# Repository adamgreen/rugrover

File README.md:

# Rug Rover

## **Project on Hold**
I am putting this project on hold for a few months while I switch back to my [Robomagellan robot project](https://github.com/adamgreen/Ferdinand20/#readme) in hopes of the SRS Robothon competition being run in 2023. I will take lessons learned this year while working on my RugRover and apply them to my Robomagellan bot, Ferdinand20.

## Project Overview

When I first started pursuing robotics as a hobby back in the late 1990s, one of the first books I read was ["Mobile Robots: Inspiration to Implementation" by Joseph L. Jones and Anita M. Flynn](https://www.amazon.com/Mobile-Robots-Inspiration-Implementation-Second/dp/B0087P7X2S). I just read it again recently and the core lessons covered by the book are just as useful today as they were back at that time even though some of the technology discussed is now a bit out of date. The mechanical, electrical, motor physics, and behavior based programming topics covered are all still relevant. The Motorola 68HC11 microcontroller and Interactive C programming language are examples of some of the more dated topics.

After reading the book for the first time, I ordered one of the [Rug Warrior Pro kits](http://www.robotbooks.com/rug_warrior.htm) and assembled it. I enjoyed putting it together but never did a lot of experimentation with it as I never really got one of the wheel encoders to work properly. It seemed to pick up noise from the motor as erroneous encoder tick counts.

Having recently reread the book, I thought it would be fun to build a comparable robot using more recent technology. This Rug Rover project is my attempt to build such a robot. It features will include:
* Similar sensors/actuators:
  * Motors with encoders
  * IR proximity sensors
  * Bumper switches
  * Microphone
  * Speaker
  * Pyroelectric sensor
  * Photo Cell light level detectors
  * LCD
* Add in IR based downward facing cliff detectors so that I can run the robot in my loft and hopefully write software that stops it from trying to make a run down the stairs.
* More modern nRF52 BLE capable microcontroller:
  * Exploit the BLE capabilities of this microcontroller to enable wireless debugging and programming.
  * Program in C/C++ using GCC.
  * Debug code using GDB.
* Mechanical components will be designed in CAD and 3D printed.
* Use KiCAD to design a custom PCB for this bot. The first iteration of the PCB will be a shield for a nRF52 development kit that I already own. Later I can design a new PCB that uses a small nRF52 module, like those [offered by Adafruit](https://www.adafruit.com/product/4077).

## Reading List
In addition to reading ["Mobile Robots: Inspiration to Implementation" by Joseph L. Jones and Anita M. Flynn](https://www.amazon.com/Mobile-Robots-Inspiration-Implementation-Second/dp/B0087P7X2S) I have also read a few other books to learn more about robot design, building, and programming while working on this project:

**Note:** A free PDF version of the **Navigating Mobile Robots book by Borenstein et al** shown above is also available [here](http://www-personal.umich.edu/~johannb/Papers/pos96rep.pdf).

## Bill of Materials
| Quantity | Part Name / Link |
|---|-|
| 2 | [63:1 Metal Gearmotor 20Dx43L mm 6V CB with Extended Motor Shaft](https://www.pololu.com/product/3714) |
| 1 | [Magnetic Encoder Pair Kit for 20D mm Metal Gearmotors, 20 CPR, 2.7-18V](https://www.pololu.com/product/3499) |
| 2 | [TB9051FTG Single Brushed DC Motor Driver Carrier](https://www.pololu.com/product/2997) |
| 1 | [Pololu Multi-Hub Wheel w/Inserts for 3mm and 4mm Shafts - 80×10mm, Black, 2-Pack](https://www.pololu.com/product/3690) |
| 1 | [Supporting Swivel Caster Wheel - 1.3" Diameter](https://www.adafruit.com/product/2942) |
| 1 | [Pololu 3.3V, 500mA Step-Down Voltage Regulator D24V5F3](https://www.pololu.com/product/2842) |
| 1 | [Pololu 5V, 500mA Step-Down Voltage Regulator D24V5F5](https://www.pololu.com/product/2843) |
| 1 | [Pololu 12V Step-Up Voltage Regulator U3V40F12](https://www.pololu.com/product/4016) |
| 1 | [Adafruit I2S 3W Class D Amplifier Breakout - MAX98357A](https://www.adafruit.com/product/3006) |
| 1 | [Mini Oval Speaker - 8 Ohm 1 Watt](https://www.adafruit.com/product/3923) |
| 1 | [Adafruit PDM MEMS Microphone Breakout](https://www.adafruit.com/product/3492) |
| 1 | [Graphical OLED Display: 128x64, 1.3", White, SPI](https://www.pololu.com/product/3760) |
| 1 | [MCP23018T-E/SO - I/O Expander 16 I²C 3.4 MHz 28-SOIC](https://www.digikey.com/en/products/detail/microchip-technology/MCP23018T-E-SO/2002549) |
| 2 | [VL6180X Time-of-Flight Distance Sensor Carrier with Voltage Regulator, 60cm max](https://www.pololu.com/product/2489) |
| 5 | [VL53L1X Time-of-Flight Distance Sensor Carrier with Voltage Regulator, 400cm Max](https://www.pololu.com/product/3415) |
| 2 | [Photo cell (CdS photoresistor)](https://www.adafruit.com/product/161) |
| 3 | [Snap-Action Switch with 15.6mm Bump Lever: 3-Pin, SPDT, 5A](https://www.pololu.com/product/1405) |
| 1 | [PIR Motion Sensor](https://www.pololu.com/product/2731) |
| 1 | [Adafruit Precision NXP 9-DOF Breakout Board - FXOS8700 + FXAS21002](https://www.adafruit.com/product/3463) |
| 1 | [Diode Schottky 60 V 7A Surface Mount TO-277A ](https://www.digikey.com/en/products/detail/vishay-general-semiconductor-diodes-division/SS10P6-M3-86A/2152231) |
| 1 | [Toggle Switch SPDT Through Hole](https://www.digikey.com/en/products/detail/e-switch/100SP1T1B4M2QE/378824?s=N4IgTCBcDaIKIHEwGYCsqC0A5AIiAugL5A) |
| 1 | [Rechargeable NiMH Battery Pack: 6.0 V, 2200 mAh, 3+2 AA Cells, JR Connector](https://www.pololu.com/product/2224) |
| 2 | [Red Dirt Derby 2 oz Tungsten Putty Weights](https://www.amazon.com/Red-Dirt-Derby-Tungsten-Pinewood/dp/B06Y5FDLL6) |
| 1 | [1/4" OD Black Latex Tubing for Bumper Skirt Standoffs](https://www.amazon.com/LATEX-TUBING-602-BLACK-10FT/dp/B074NCLZSW) |
| 1 | [Nordic Semiconductor nRF52 Development Kit](https://www.digikey.com/en/products/detail/nordic-semiconductor-asa/NRF52-DK/5773879) |
| X | Already owned 0805 passives, 0.1" headers, etc. |
| X | Already owned M2, M2.5, and M3 hardware |

**Notes:** I didn't end up with enough spare pins on version 1 of the PCB to connect the microphone and I2S audio components. I will experiment with these devices off of the robot for now and then add them on the next revision of the board.

## Mechanical Design
When it comes to robot building, the mechanical portions are my weakest area. On some other robot projects I have started with software drivers and then never got around to even starting on the mechanical portions since I wasn't really looking forward to it. Best to get it out of the way first on this project. Doing it first also means that I have something physical to look at and hold earlier in the project to help keep me motivated.

**Mechanical Highlights:**
* 3D print the mechanical parts for this robot in PETG.
* Use OpenSCAD for the 3D design.
* The following parts will be mounted to the underside of the robot chassis:
  * 2 x Motors
  * 1 x Caster
  * 2 x Cliff Detection Sensors (VL6180X) mounted in front of the wheels.
  * 3 x Micro Switches to detect bumper collisions.
  * 1 x 5 cell (6V) NiMH rechargeable battery.
* Chassis has holes for attachment of following parts to the topside of the chassis:
  * 5 x Standoffs for Nordic nRF52-DK Development Kit PCB to which shield with remaining sensors/actuators will be mounted.
  * 3 x Flexible Rubber Tube Standoffs to which the bumper skirt is attached, allowing bumper to move and press against micro switches when an obstacle is encountered.
  * A separate curved cylindrical 3D printed holder that goes on the back of the robot to hold ~100g of tungsten counter weight. This moves the center of mass closer to the caster so that the robot doesn't nose dive during quick decelerations. Only having room for the batteries at the front of the bot increased the need for this counterweight.
* A separate bumper skirt is printed to enclose the robot.
  * It is mounted to the chassis on flexible rubber tube standoffs like the Rug Warrior Pro.

**Lessons Learned:**
* The [caster](https://www.adafruit.com/product/2942) I used on this robot is probably too large for the size of the robot. Its size makes it difficult to concentrate the mass over the caster by placing heavy things like the batteries near it on the bottom. I now see why the original RugWarrior Pro used the smaller non-swiveling ball caster. It took up less space and allowed the battery pack to be placed between the axle and the caster.
* [Tungsten putty](https://www.amazon.com/Red-Dirt-Derby-Tungsten-Pinewood/dp/B06Y5FDLL6) is actually a soft moving liquid. The putty I placed in the cylindrical 3D printed holder at the back of the robot leaked out over time and some of it flowed out into the rear micro switch. I was able to take the robot apart and clean up the leaked putty. I designed and printed a bottom for the holder that I welded in place with a soldering iron to contain the tungsten putty inside.

## Electronics Design
Once I had the mechanical design mostly figured out, I moved onto the design of the electronics in [KiCad](https://www.kicad.org).

**Electronic Highlights:**
* The initial version of the electronics will use the [Nordic nRF52 DK](https://www.nordicsemi.com/Products/Development-hardware/nrf52-dk) as its base and the custom robot electronics will be added as a custom shield.
* The shield design is 4-layer to make it easier to route the signals all around the board without worrying about ground and power. The layout is a bit complicated as the Arduino header format used by the nRF52 DK has most of the signals on one side of the board but I want to place input/output connectors on both sides of the board.
* Most of the sensors and actuators are connected to the PCB via 0.1" headers.
* Version 1 of the shield includes:
  * Dual TB9051FTG motor controllers
  * Quadrature motor encoders
  * Dual photo cells
  * PIR motion sensor
  * Three switches for bumper skirt obstacle detection
  * SPI based OLED screen
  * One I2C bus for connection to:
    * 5 x VL53L1X ToF Obstacle Detection Sensors (3 front facing & 2 back facing).
    * 2 x VL6180X ToF Cliff Detection Sensors mounted in front of the wheels.
    * 1 x Adafruit Precision NXP 9-DOF IMU
    * 1 x 16 channel MCP23018 I/O port expander used for:
      * Asserting VL53L1X and VL6180X XSHUT pins to init each one separately and give them unique I2C addresses.
      * Reading of the multiple VL53L1X and VL6180X GPIO pins.
 * Multiple voltage supplies:
   * 6V Directly from Batteries for Motors
   * 5V from Buck Regulator for TB9051FTG Motor Controllers
   * 12V from Boost Regulator for PIR Sensor
   * 3.3V from Buck Regulator for rest of Electronics

</br>

[Schematic PDF](hardware/shield.pdf)</br>

## Software
Once the mechanical and electronics were far enough along I could start writing the software. This should be where I spend the most amount of time. I will provide links to notes about each software component as I write its code.

**Software Components:**
* [mriblue Debug Monitor](mriblue/README.md#mriblue): A FLASH resident bootloader and debug monitor that runs on the nRF52832 to enable wireless debugging and programming over Bluetooth Low Energy (BLE) from GDB.
* [SH1106 SPI based OLED Driver](software/OLED_SH1106/):
  * An [Adafruit GFX](https://github.com/adafruit/Adafruit-GFX-Library) based display driver.
  * The drawing primitives just modify an in-memory version of the display's frame buffer.
  * A separate refresh() method is used to copy that frame buffer to the SH1106 OLED driver.
  * The refresh() copy makes use of the nRF52's SPI Master peripheral's EasyDMA functionality to perform most of this SPI transfer in the background with little CPU intervention. The CPU is just used to setup the transfer for each of the 8 frame buffer pages.
* [QuadratureDecoderHardware](software/QuadratureDecoder/QuadratureDecoderHardware.h): This driver uses the QDEC peripheral on the nRF52832 to count quadrature encoder ticks. It requires almost no CPU cycles but there is only 1 instance on the microcontroller so I use it for the left encoder only.
* [QuadratureDecoderSoftware](software/QuadratureDecoder/QuadratureDecoderSoftware.h): This driver uses the GPIOTE to fire an ISR on each edge of both the A and B signals from a quadrature encoder. The ISR uses the previous and current encoder signal states to determine if the count should be incremented or decremented. A maximum of 4 encoders can make use of this library if nothing else is making use of the nRF52's 8 GPIOTE channels. The driver needs 2 GPIOTE channels for each encoder, 1 per encoder signal.
* [SAADCScanner](software/SAADCScanner/SAADCScanner.h): This driver runs in the background, reading the specified analog channels (up to 8 on the nRF52832) in a loop using the nRF52's SAADC peripheral:
  * At the end of each loop, an ISR is triggered to process the most current readings. This allows for minimal CPU overhead.
  * It can be configured for manual scanning rather than continuously scanning in the background. I am currently using it this way since it would run at 50kHz in auto mode and the ISR kept showing up in call stacks when I profiled the code.
  * The application can read out a channel's value at a rate slower than the ISR firing rate. The returned structure contains the minimum, maximum, and mean values seen since the last read.
  * The application can also specify trigger limits for the minimum and/or maximum analog values to be expected. Readings outside of these limits will be tracked in the returned structure and can also trigger a callback to a caller provided ISAADCScannerNotification interface.
  * This driver is currently only used to monitor the motor currents for each wheel. In the future it can be used to monitor the light levels detected by the 2 photocells.
* [DualTB9051FTGDrivers](software/DualTB9051FTGDrivers/DualTB9051FTGDrivers.h): This driver allows for the control of 2 Toshiba TB9051FTG H-bridge chips, one for each motor on the robot. It uses 4 channels of the nRF52's PWM peripheral to control the torque and speed of the motors with minimal CPU intervention.
* [GlobalTimer](software/GlobalTimer/GlobalTimer.h): Uses TIMER2 to implement an Arduino like ```micros()``` API to return a 32-bit value indicating the number of microseconds since reset.
* [PID](software/PID/PID.h): Header only class that implements a PID (proportional, integral, derivative) algorithm. It is inspired by [Brett Beauregard's Arduino PID Library](https://github.com/br3ttb/Arduino-PID-Library/) and the [PID e-book available on controlguru](http://www.controlguru.com).
* [DifferentialDrive](software/DifferentialDrive/DifferentialDrive.h): This driver implements closed loop control of RugRover's differential drive. It is built on top of the **DualTB9051FTGDrivers** and Quadrature Decoder libraries. It also has a getStats() method which exposes internal state of the motors, encoders, and PID algorithm to the user:
  * The requested velocity and the actual measured velocity of each wheel.
  * The running total of encoder ticks for each wheel.
  * The motor power (-100% to 100%) being used for each wheel.
  * The most recent motor current measurement (mA) taken for each wheel.
  * The maximum motor current measurement (mA) taken for each wheel so far.
  * Whether any motor faults or over-current events have been detected by the motor drivers.
  * The mAh consumed by the motors since reset.
  * A flag to indicate whether the PID is running in manual or auto mode.
* [Navigate](software/Navigate/README.md#navigate-class): Class used to navigate between a list of user specified waypoints and track the real world location of the robot based on wheel odometry.
* [CircularBuffer](software/CircularBuffer/CircularBuffer.h): Generic lock-free circular buffer that supports multiple producers and consumers.
* [I2CAsync](software/I2CAsync/I2CAsync.h): This driver makes it easier to use the nRF52's TWIM peripheral asynchronously. It makes use of the `CircularBuffer` to allow ISRs running at different interrupt priorities to communicate with several different I2C devices.
* [AdafruitPrecision9DoF](software/AdafruitPrecision9DoF/AdafruitPrecision9DoF.h): This driver uses the `I2CAsync` driver to communicate with the `FXOS8700CQ` accelerometers/magnetometers and the `FXAS21002C` gyros.
  * The desired refresh rate (100Hz, 200Hz, or 400Hz) is specified in the constructor.
  * The `FXOS8700CQ` will pull a pin low when the next sample is ready at the specified rate.
  * This falling edge generates an interrupt that causes the next I2C reads of the accelerometers, magnetometers, and gyros to be queued up in the `I2CAsync` queue.
  * The `getRawSensorValues()` method, typically called from the main thread, will block until all of the queued up reads are completed.
* [OrientationKalmanFilter](software/KalmanFilter/OrientationKalmanFilter.h): Implements a Kalman filter which takes the raw accelerometer, magnetometer, and gyro measurements from the `AdafruitPrecision9DoF` object and generates a 3D orientation quaternion.
  * It also contains a method which can extract the compass heading from this 3D orientation as well.
  * The code for this filter was based on what I learned from reading ["Kalman Filter for Beginners with MATLAB Examples" by Phil Kim](https://www.amazon.com/Kalman-Filter-Beginners-MATLAB-Examples/dp/1463648359). The system model used in this filter came from Chapter 13 of this book.
  * I documented many of the required calibration steps [earlier while working on my Ferdinand14 project](https://github.com/adamgreen/Ferdinand14#august-19-2014).
  * The [processing/calibration folder](processing/calibration/) contains a port of the calibration program which will work with this robot. The robot does need to be running the "Test IMU Raw" option from the debug menu to send the required measurements to this calibration program.
  * The [processing/orientation folder](processing/orientation/) contains a program that visualizes the 3D orientation of the robot in real time. The robot needs to be running the "Test IMU Orientation" option from the debug menu in order to send the required quaternion data over BLE to this program.
  * Both of the processing programs above use a TCP/IP socket to connect to the `mriblue` program on port 3334. This gives it access to extra data sent from the robot over BLE that isn't meant for GDB.
* [HeadingKalmanFilter](software/KalmanFilter/HeadingKalmanFilter.h): Implements a Kalman filter which fuses Z axis gyro angular rate measurements with angle heading change measurements calculated from wheel odometry.
  * The code for this filter was also based on what I learned from reading ["Kalman Filter for Beginners with MATLAB Examples" by Phil Kim](https://www.amazon.com/Kalman-Filter-Beginners-MATLAB-Examples/dp/1463648359).
  * The system model used by this filter was one I created on my own. It tracks:
    * The current heading angle in radians.
    * The current gyro angular turn rate in radians/sec.
    * The estimate of the gyro drift in radians/sec. Having an estimate of this value allows for the filter to obtain a more accurate turn rate from the gyro than possible otherwise.
  * I determined the first two variance values to place in the Q matrix by setting the `DEBUG_CALCULATE_STATS_FOR_SYSTEM_MODEL` macro to true in [main.cpp](software/main.cpp) so that it would dump stats about how much this model tended to deviate from the real world while just using wheel odometry. I then set the variance for the drift parameter to 0.0 since the model maintains it as a constant and in the real world it should vary slowly over time.
  * The `GYRO_ERROR` was calculated and dumped by the orientation.pde utility while I was calibrating the IMU for the OrientationKalmanFilter.
  * I estimate that the `ODOMETRY_ERROR` error is typically the result of a +/- 1 encoder tick's influence on the wheel odometry calculation of the heading angle delta.

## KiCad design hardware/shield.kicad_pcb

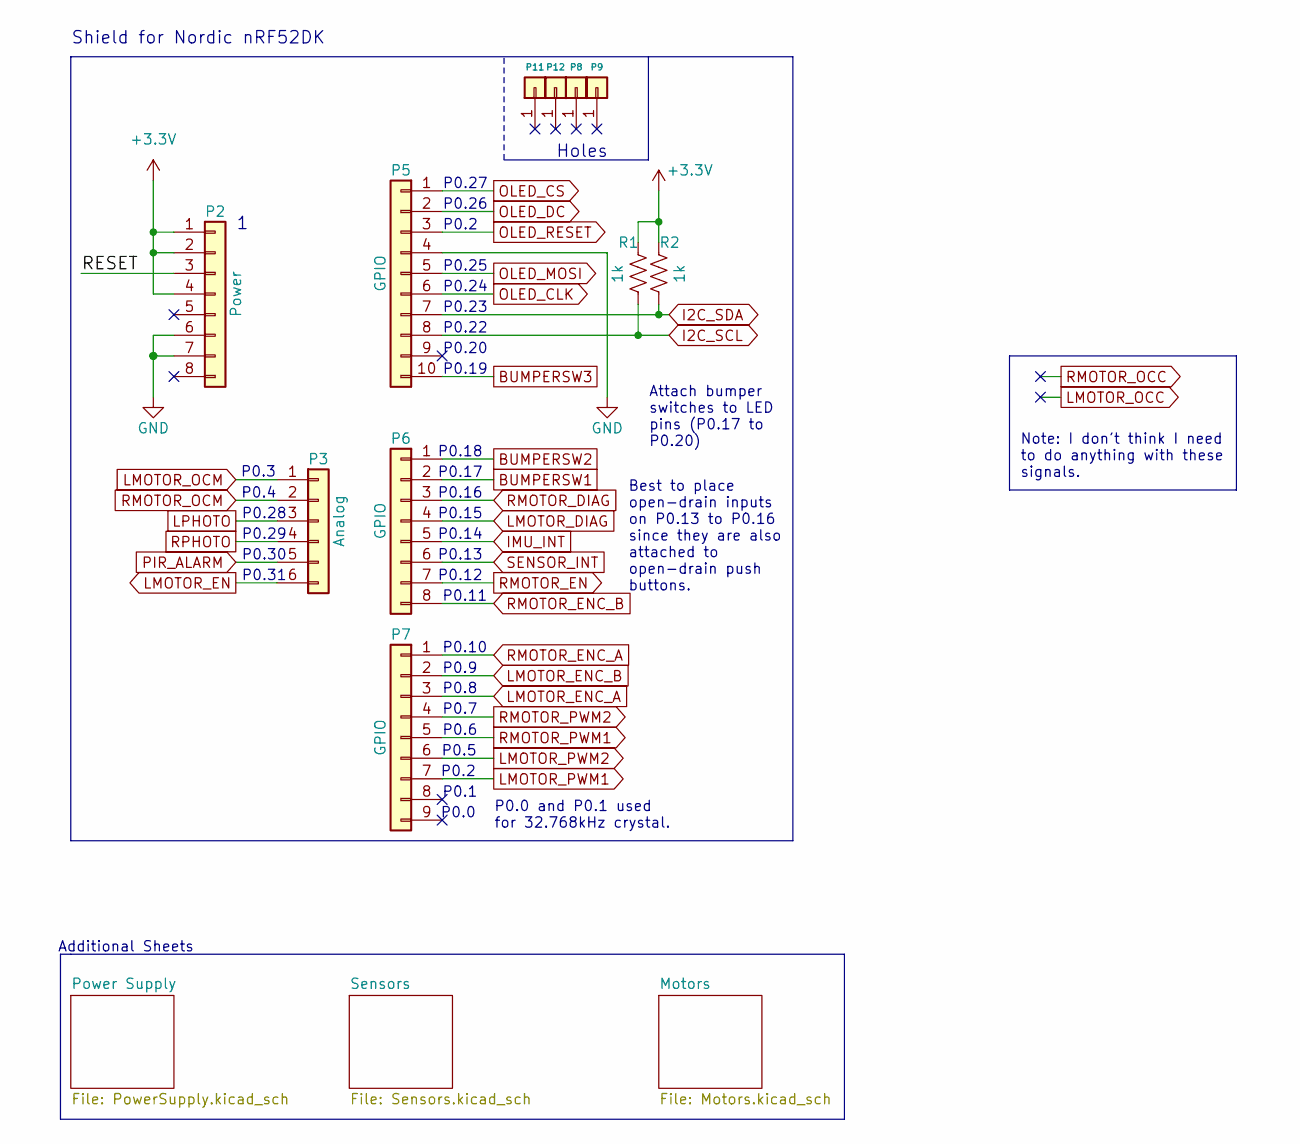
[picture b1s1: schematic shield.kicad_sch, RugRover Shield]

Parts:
P2: Power; PinHeader_1x08_P2.54mm_Vertical
P3: Analog; PinHeader_1x06_P2.54mm_Vertical
P5: GPIO; PinHeader_1x10_P2.54mm_Vertical
P6: GPIO; PinHeader_1x08_P2.54mm_Vertical
P7: GPIO; PinHeader_1x09_P2.54mm_Vertical
P8, P9, P11, P12: CONN_01X01; Arduino_1pin
R1, R2: 1k; R_0805_2012Metric_Pad1.20x1.40mm_HandSolder

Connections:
+3V3: P2.1, P2.2, P2.4, R1.1, R2.1; also elsewhere on the board
/RESET: P2.3
BUMPERSW1: P6.2; also elsewhere on the board
BUMPERSW2: P6.1; also elsewhere on the board
BUMPERSW3: P5.10; also elsewhere on the board
GND: P2.6, P2.7, P5.4; also elsewhere on the board
I2C_SCL: P5.8, R1.2; also elsewhere on the board
I2C_SDA: P5.7, R2.2; also elsewhere on the board
IMU_INT: P6.5; also elsewhere on the board
LMOTOR_DIAG: P6.4; also elsewhere on the board
LMOTOR_EN: P3.6; also elsewhere on the board
LMOTOR_ENC_A: P7.3; also elsewhere on the board
LMOTOR_ENC_B: P7.2; also elsewhere on the board
LMOTOR_OCM: P3.1; also elsewhere on the board
LMOTOR_PWM1: P7.7; also elsewhere on the board
LMOTOR_PWM2: P7.6; also elsewhere on the board
LPHOTO: P3.3; also elsewhere on the board
OLED_CLK: P5.6; also elsewhere on the board
OLED_CS: P5.1; also elsewhere on the board
OLED_DC: P5.2; also elsewhere on the board
OLED_MOSI: P5.5; also elsewhere on the board
OLED_RESET: P5.3; also elsewhere on the board
PIR_ALARM: P3.5; also elsewhere on the board
RMOTOR_DIAG: P6.3; also elsewhere on the board
RMOTOR_EN: P6.7; also elsewhere on the board
RMOTOR_ENC_A: P7.1; also elsewhere on the board
RMOTOR_ENC_B: P6.8; also elsewhere on the board
RMOTOR_OCM: P3.2; also elsewhere on the board
RMOTOR_PWM1: P7.5; also elsewhere on the board
RMOTOR_PWM2: P7.4; also elsewhere on the board
RPHOTO: P3.4; also elsewhere on the board
SENSOR_INT: P6.6; also elsewhere on the board

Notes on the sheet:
P0.24
P0.11
Attach bumper switches to LED pins (P0.17 to P0.20)
P0.14
P0.9
Note: I don't think I need to do anything with these signals.
P0.19
P0.12
P0.22
P0.30
P0.18
P0.5
P0.2
P0.20
Best to place open-drain inputs on P0.13 to P0.16 since they are also attached to open-drain push buttons.
P0.6
P0.23
P0.16
P0.17
P0.0 and P0.1 used for 32.768kHz crystal.
P0.4
P0.1
P0.31
P0.27
P0.15
P0.26
P0.3
P0.29
P0.8
P0.7
Holes
P0.13
P0.10
Additional Sheets
P0.25
P0.0
P0.28
Shield for Nordic nRF52DK

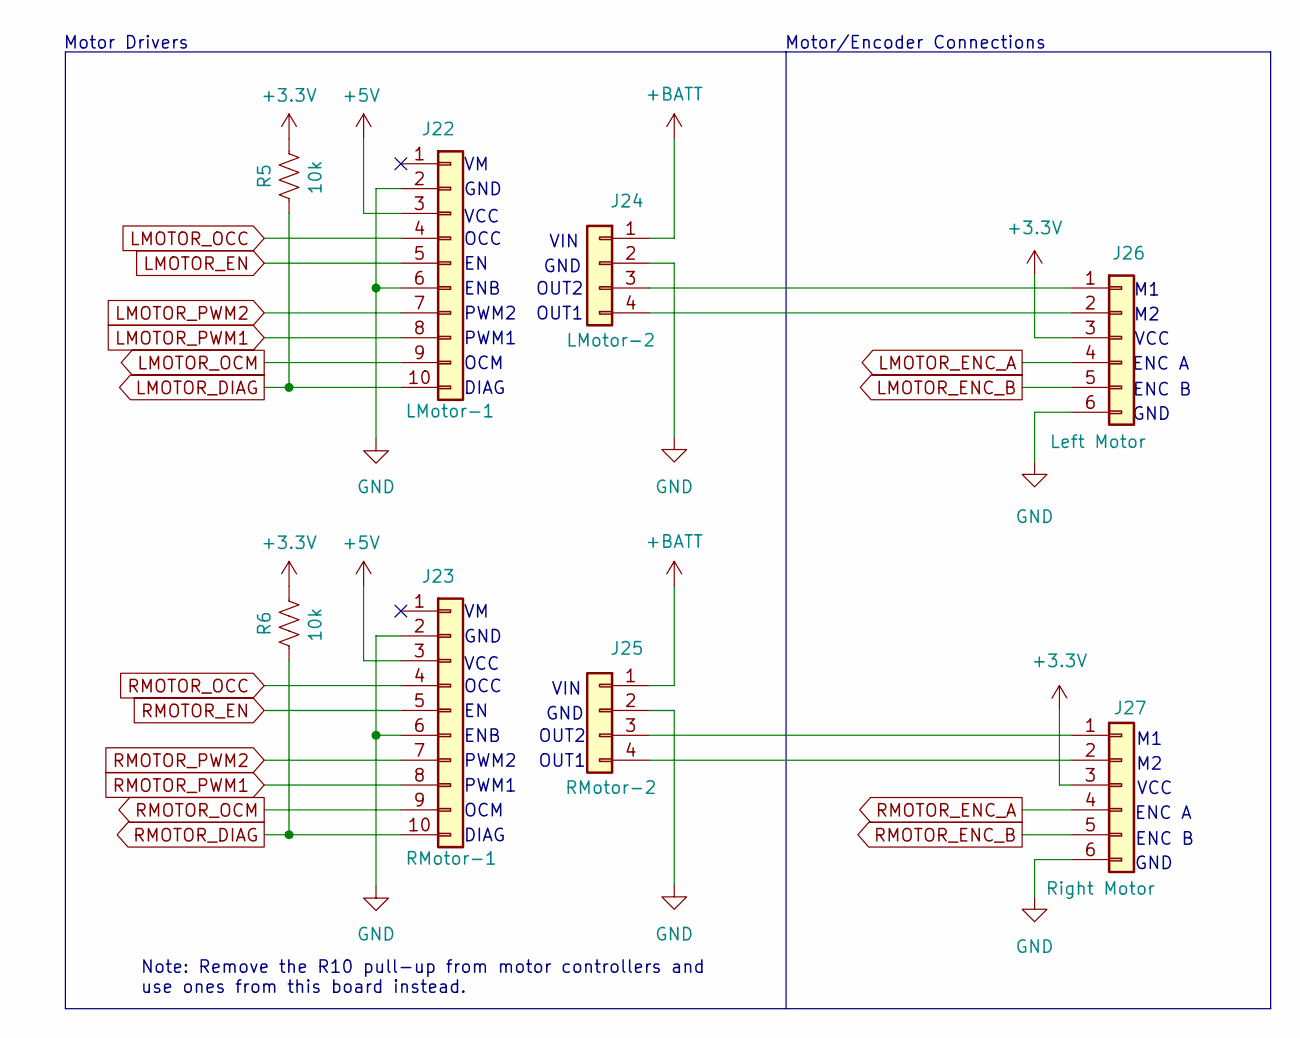
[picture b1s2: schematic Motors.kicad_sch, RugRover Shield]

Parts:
J22: LMotor-1; PinSocket_1x10_P2.54mm_Vertical
J23: RMotor-1; PinSocket_1x10_P2.54mm_Vertical
J24: LMotor-2; PinSocket_1x04_P2.54mm_Vertical
J25: RMotor-2; PinSocket_1x04_P2.54mm_Vertical
J26: Left Motor; PinSocket_1x06_P2.54mm_Horizontal
J27: Right Motor; PinSocket_1x06_P2.54mm_Horizontal
R5, R6: 10k; R_0805_2012Metric_Pad1.20x1.40mm_HandSolder

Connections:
+3V3: J26.3, J27.3, R5.2, R6.2; also elsewhere on the board
+5V: J22.3, J23.3; also elsewhere on the board
+BATT: J24.1, J25.1; also elsewhere on the board
GND: J22.2, J22.6, J23.2, J23.6, J24.2, J25.2, J26.6, J27.6; also elsewhere on the board
LMOTOR_DIAG: J22.10, R5.1; also elsewhere on the board
LMOTOR_EN: J22.5; also elsewhere on the board
LMOTOR_ENC_A: J26.4; also elsewhere on the board
LMOTOR_ENC_B: J26.5; also elsewhere on the board
LMOTOR_OCC: J22.4
LMOTOR_OCM: J22.9; also elsewhere on the board
LMOTOR_PWM1: J22.8; also elsewhere on the board
LMOTOR_PWM2: J22.7; also elsewhere on the board
unnamed: J24.3, J26.1
unnamed: J24.4, J26.2
unnamed: J25.3, J27.1
unnamed: J25.4, J27.2
RMOTOR_DIAG: J23.10, R6.1; also elsewhere on the board
RMOTOR_EN: J23.5; also elsewhere on the board
RMOTOR_ENC_A: J27.4; also elsewhere on the board
RMOTOR_ENC_B: J27.5; also elsewhere on the board
RMOTOR_OCC: J23.4
RMOTOR_OCM: J23.9; also elsewhere on the board
RMOTOR_PWM1: J23.8; also elsewhere on the board
RMOTOR_PWM2: J23.7; also elsewhere on the board

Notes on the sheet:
GND
OUT2
ENC A
PWM2
DIAG
VCC
ENB
ENC B
PWM1
Note: Remove the R10 pull-up from motor controllers and use ones from this board instead.
VIN
Motor Drivers
OUT1
OCC
Motor/Encoder Connections
OCM

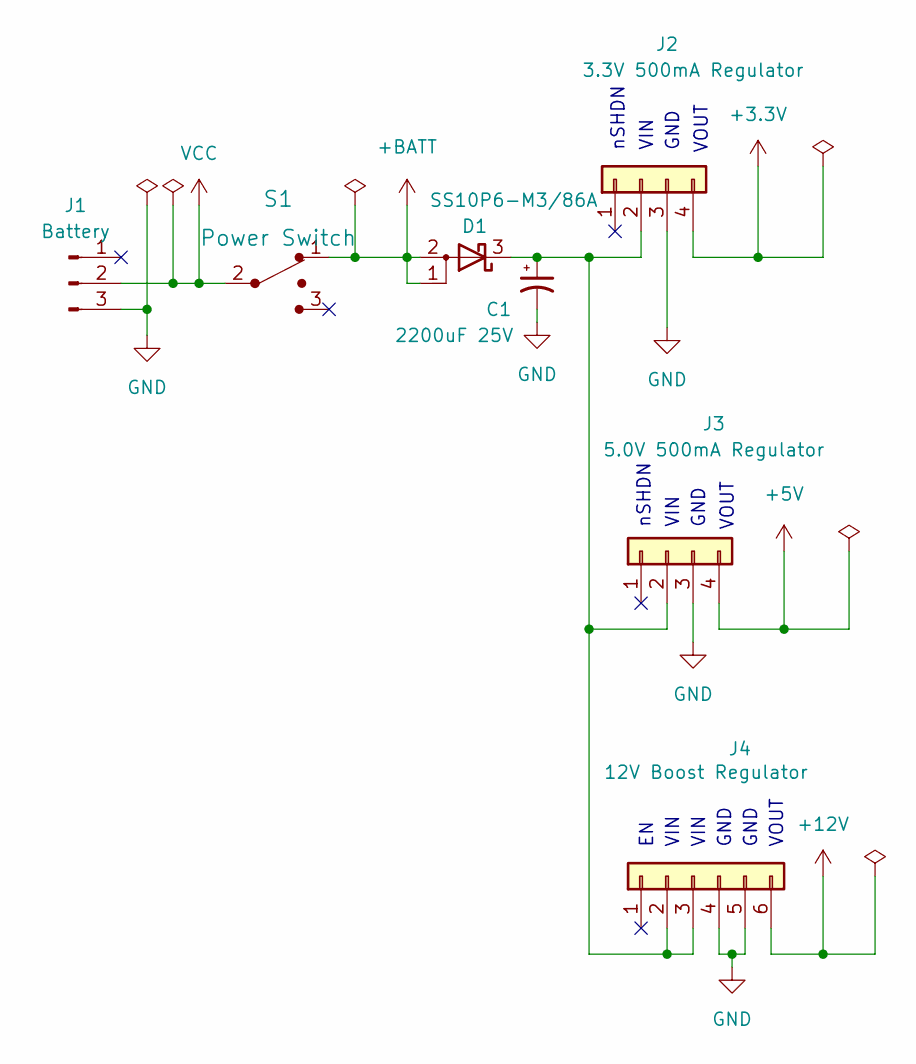
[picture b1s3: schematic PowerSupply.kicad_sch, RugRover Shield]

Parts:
C1: 2200uF 25V; CP_Radial_D13.0mm_P5.00mm
D1: SS10P6-M3/86A; TO-277A
J1: Battery; PinHeader_1x03_P2.54mm_Horizontal
J2: 3.3V 500mA Regulator; PinSocket_1x04_P2.54mm_Vertical
J3: 5.0V 500mA Regulator; PinSocket_1x04_P2.54mm_Vertical
J4: 12V Boost Regulator; PinSocket_1x06_P2.54mm_Vertical
S1: Power Switch; Toggle_Switch_100SP1T1B4M2QE; MPN 100SP1T1B4M2QE; Digi-Key_PN EG2355-ND

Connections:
+3V3: J2.4; also elsewhere on the board
+5V: J3.4; also elsewhere on the board
+12V: J4.6; also elsewhere on the board
+BATT: D1.1 (A), D1.2 (A), S1.1; also elsewhere on the board
GND: C1.2, J1.3, J2.3, J3.3, J4.4, J4.5; also elsewhere on the board
unnamed: C1.1, D1.3 (K), J2.2, J3.2, J4.2, J4.3
VCC: J1.2, S1.2 (Com)

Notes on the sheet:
VIN
GND
VOUT
nSHDN

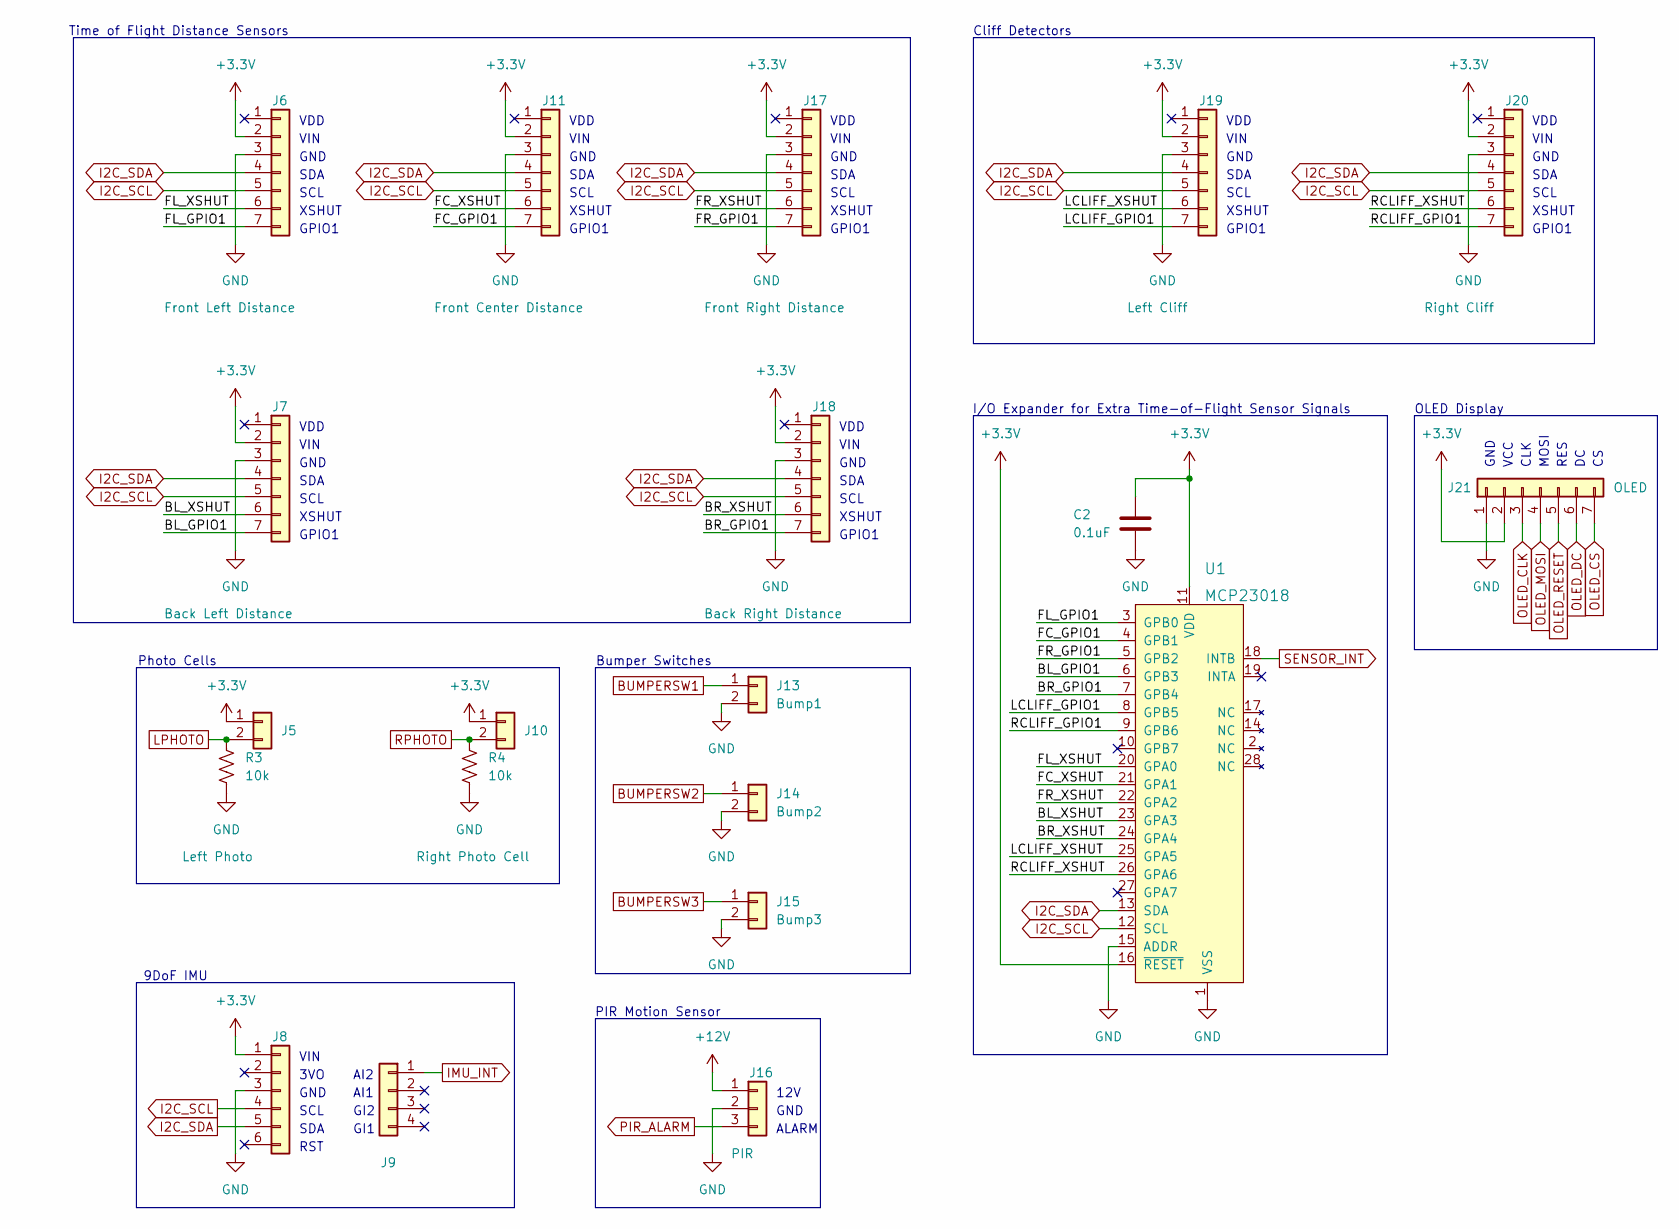
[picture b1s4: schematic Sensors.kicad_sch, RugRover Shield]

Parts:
C2: 0.1uF; C_0805_2012Metric_Pad1.18x1.45mm_HandSolder
J5: Left Photo; PinSocket_1x02_P2.54mm_Vertical
J6: Front Left Distance; PinSocket_1x07_P2.54mm_Vertical
J7: Back Left Distance; PinSocket_1x07_P2.54mm_Vertical
J8: IMU-1; PinSocket_1x06_P2.54mm_Vertical
J9: IMU-2; PinSocket_1x04_P2.54mm_Vertical
J10: Right Photo Cell; PinSocket_1x02_P2.54mm_Vertical
J11: Front Center Distance; PinSocket_1x07_P2.54mm_Vertical
J13: Bump1; PinSocket_1x02_P2.54mm_Horizontal
J14: Bump2; PinSocket_1x02_P2.54mm_Horizontal
J15: Bump3; PinSocket_1x02_P2.54mm_Horizontal
J16: PIR; PinSocket_1x03_P2.54mm_Vertical
J17: Front Right Distance; PinSocket_1x07_P2.54mm_Vertical
J18: Back Right Distance; PinSocket_1x07_P2.54mm_Vertical
J19: Left Cliff; PinSocket_1x07_P2.54mm_Horizontal
J20: Right Cliff; PinSocket_1x07_P2.54mm_Horizontal
J21: OLED; PinSocket_1x07_P2.54mm_Vertical
R3, R4: 10k; R_0805_2012Metric_Pad1.20x1.40mm_HandSolder
U1: MCP23018; SOIC-28W_7.5x17.9mm_P1.27mm; MPN MCP23018-E/SP; Digi-Key_PN MCP23018-E/SP-ND

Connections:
+3V3: C2.1, J5.1, J6.2, J7.2, J8.1, J10.1, J11.2, J17.2, J18.2, J19.2, J20.2, J21.2, U1.11 (VDD), U1.16 (~RESET); also elsewhere on the board
+12V: J16.1; also elsewhere on the board
/Sensors/BL_GPIO1: J7.7, U1.6 (GPB3)
/Sensors/BL_XSHUT: J7.6, U1.23 (GPA3)
/Sensors/BR_GPIO1: J18.7, U1.7 (GPB4)
/Sensors/BR_XSHUT: J18.6, U1.24 (GPA4)
/Sensors/FC_GPIO1: J11.7, U1.4 (GPB1)
/Sensors/FC_XSHUT: J11.6, U1.21 (GPA1)
/Sensors/FL_GPIO1: J6.7, U1.3 (GPB0)
/Sensors/FL_XSHUT: J6.6, U1.20 (GPA0)
/Sensors/FR_GPIO1: J17.7, U1.5 (GPB2)
/Sensors/FR_XSHUT: J17.6, U1.22 (GPA2)
/Sensors/LCLIFF_GPIO1: J19.7, U1.8 (GPB5)
/Sensors/LCLIFF_XSHUT: J19.6, U1.25 (GPA5)
/Sensors/RCLIFF_GPIO1: J20.7, U1.9 (GPB6)
/Sensors/RCLIFF_XSHUT: J20.6, U1.26 (GPA6)
BUMPERSW1: J13.1; also elsewhere on the board
BUMPERSW2: J14.1; also elsewhere on the board
BUMPERSW3: J15.1; also elsewhere on the board
GND: C2.2, J6.3, J7.3, J8.3, J11.3, J13.2, J14.2, J15.2, J16.2, J17.3, J18.3, J19.3, J20.3, J21.1, R3.2, R4.2, U1.1 (VSS), U1.15 (ADDR); also elsewhere on the board
I2C_SCL: J6.5, J7.5, J8.4, J11.5, J17.5, J18.5, J19.5, J20.5, U1.12 (SCL); also elsewhere on the board
I2C_SDA: J6.4, J7.4, J8.5, J11.4, J17.4, J18.4, J19.4, J20.4, U1.13 (SDA); also elsewhere on the board
IMU_INT: J9.1; also elsewhere on the board
LPHOTO: J5.2, R3.1; also elsewhere on the board
OLED_CLK: J21.3; also elsewhere on the board
OLED_CS: J21.7; also elsewhere on the board
OLED_DC: J21.6; also elsewhere on the board
OLED_MOSI: J21.4; also elsewhere on the board
OLED_RESET: J21.5; also elsewhere on the board
PIR_ALARM: J16.3; also elsewhere on the board
RPHOTO: J10.2, R4.1; also elsewhere on the board
SENSOR_INT: U1.18 (INTB); also elsewhere on the board

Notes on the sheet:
VIN
SDA
I/O Expander for Extra Time-of-Flight Sensor Signals
GND
GI1
XSHUT
GPIO1
RES
VDD
12V
CLK
SCL
Photo Cells
RST
Time of Flight Distance Sensors
AI1
OLED Display
GI2
PIR Motion Sensor
Bumper Switches
9DoF IMU
AI2
ALARM
3VO
Cliff Detectors
MOSI
VCC

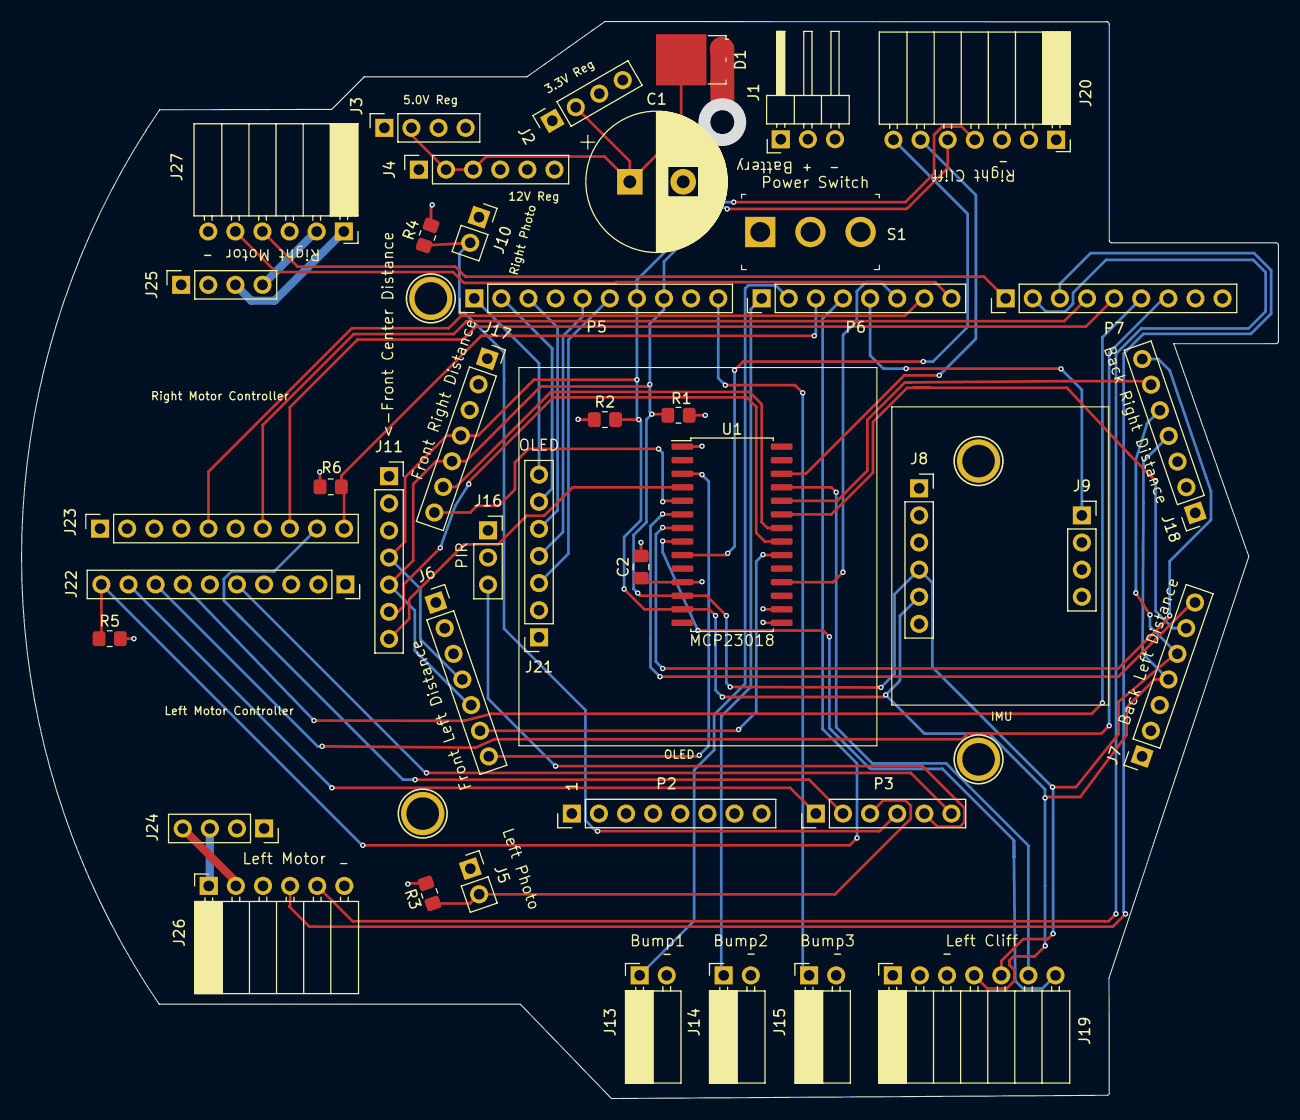
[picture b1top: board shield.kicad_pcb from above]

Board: 4 copper layers, 117.7 x 100.9 mm, 46 parts (0 on the bottom side), 54 nets.

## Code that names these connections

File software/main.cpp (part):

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   The hardware pin connections are:
   nRF52 Pin Number     Pin Name                Pin Description
          0.24          OLED_SCK_PIN            OLED Board - CLK
          0.25          OLED_MOSI_PIN           OLED Board - MOS
          0.26          OLED_DC_PIN             OLED Board - DC
          0.27          OLED_CS_PIN             OLED Board - CS
          0.2           OLED_RESET_PIN          OLED Board - RES
    ------------------------------------------------------------------------
          0.22          I2C_SCL_PIN             I2C Bus - SCL - Multiple Devices
          0.23          I2C_SDA_PIN             I2C Bus - SDA - Multiple Devices
    ------------------------------------------------------------------------
          0.14          IMU_INT_PIN             9DoF IMU - AINT2
    ------------------------------------------------------------------------
          0.8           LMOTOR_ENCODER_A_PIN    Left Motor Encoder A
          0.9           LMOTOR_ENCODER_B_PIN    Left Motor Encoder B
          0.10          RMOTOR_ENCODER_A_PIN    Right Motor Encoder A
          0.11          RMOTOR_ENCODER_B_PIN    Right Motor Encoder B
    ------------------------------------------------------------------------
          0.31          LMOTOR_EN_PIN           Left Motor Driver - EN
          0.21          LMOTOR_PWM1_PIN         Left Motor Driver - PWM1
          0.5           LMOTOR_PWM2_PIN         Left Motor Driver - PWM2
          0.15          LMOTOR_DIAG_PIN         Left Motor Driver - DIAG
          0.3           LMOTOR_OCM_PIN          Left Motor Driver - OCM
          0.12          RMOTOR_EN_PIN           Right Motor Driver - EN
          0.6           RMOTOR_PWM1_PIN         Right Motor Driver - PWM1
          0.7           RMOTOR_PWM2_PIN         Right Motor Driver - PWM2
          0.16          RMOTOR_DIAG_PIN         Right Motor Driver - DIAG
          0.4           RMOTOR_OCM_PIM          Right Motor Driver - OCM

*/
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
// Pins connected to the SPI signals used by the SH1106 OLED driver.
#define OLED_SCK_PIN    24
#define OLED_MOSI_PIN   25
#define OLED_CS_PIN     27
#define OLED_DC_PIN     26
#define OLED_RESET_PIN  2

// The I2C (TWI) peripheral instance to use for communicating with the IMU and time of flight range sensors.
// Can't be 0 as that instance is shared with the SPI peripheral used above for the OLED.
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#define I2C_FREQUENCY   NRF_TWI_FREQ_400K

// The pins connected to the I2C (TWI) bus.
#define I2C_SCL_PIN     22
#define I2C_SDA_PIN     23

// The 9DoF IMU will issue an interrupt on the interrupt 2 pin of its accelerometer/magnetometer device when next
// sample is ready.
#define IMU_INT_PIN     14

// The sampling frequency at which the IMU should be run.
#define IMU_SAMPLE_RATE MOTOR_PID_FREQUENCY
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#define RMOTOR_ENCODER_B_PIN    11

// Pins connected to the motor drivers.
#define LMOTOR_EN_PIN       31
#define LMOTOR_PWM1_PIN     21
#define LMOTOR_PWM2_PIN     5
#define LMOTOR_DIAG_PIN     15
#define LMOTOR_OCM_PIN      3
#define RMOTOR_EN_PIN       12
#define RMOTOR_PWM1_PIN     6
#define RMOTOR_PWM2_PIN     7
#define RMOTOR_DIAG_PIN     16
#define RMOTOR_OCM_PIN      4

// Should the motor's idea of forward be reversed?
#define LMOTOR_REVERSE      true
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
// OLED Screen.
static OLED_SH1106          g_OLED(OLED_WIDTH, OLED_HEIGHT, OLED_COLUMN_OFFSET, OLED_ROW_OFFSET,
                                   &g_spiOLED, OLED_SCK_PIN, OLED_MOSI_PIN, OLED_DC_PIN);

// TWIM (I2C Master) instance used for driving IMU and time of flight sensors.
static const nrf_drv_twi_t  g_i2c = NRF_DRV_TWI_INSTANCE(I2C_INSTANCE);

// Wrapper around TWIM (I2C master) instance which adds a circular queue to manage multiple async transfers.
static I2CAsync             g_i2cAsync(&g_i2c, I2C_SCL_PIN, I2C_SDA_PIN, I2C_FREQUENCY, _PRIO_APP_MID);

// Adafruit's 9DoF IMU.
static AdafruitPrecision9DoF g_imu(&g_i2cAsync, IMU_INT_PIN, IMU_SAMPLE_RATE);

// Kalman filter used to determine 3D orientation.
static OrientationKalmanFilter g_orientation(IMU_SAMPLE_RATE, &g_imuCalibration);
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static nrf_drv_pwm_t        g_PWM = NRF_DRV_PWM_INSTANCE(0);

// Closed loop PID control of the robot's two motors.
static DifferentialDrive    g_drive(LMOTOR_EN_PIN, LMOTOR_PWM1_PIN, LMOTOR_PWM2_PIN,
                                     LMOTOR_DIAG_PIN, LMOTOR_OCM_PIN, LMOTOR_REVERSE,
                                     LMOTOR_ENCODER_A_PIN, LMOTOR_ENCODER_B_PIN,
                                     RMOTOR_EN_PIN, RMOTOR_PWM1_PIN, RMOTOR_PWM2_PIN,
                                     RMOTOR_DIAG_PIN, RMOTOR_OCM_PIN, RMOTOR_REVERSE,
                                     RMOTOR_ENCODER_A_PIN, RMOTOR_ENCODER_B_PIN,
                                     SPEED_PID_Kc, SPEED_PID_Ti, SPEED_PID_Td, MOTOR_PID_MAX_PERCENT,
                                     &g_adc,
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static void testHardWiringSomeOLEDPins()
{
    // Looks like I can just hard wire CS low and RESET high on the OLED. This will free up 2 pins.
    nrf_gpio_pin_clear(OLED_CS_PIN);
    nrf_gpio_cfg_output(OLED_CS_PIN);
    nrf_gpio_pin_set(OLED_RESET_PIN);
    nrf_gpio_cfg_output(OLED_RESET_PIN);
}

static void initI2C()
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    // Use strong sink to 0 and disable internal pull-up as we have external ones.
    // Should be done after I2C is init since it will configure the pins and before the I2C peripheral is actually
    // enabled.
    nrf_gpio_cfg(I2C_SCL_PIN, NRF_GPIO_PIN_DIR_INPUT, NRF_GPIO_PIN_INPUT_CONNECT, NRF_GPIO_PIN_NOPULL,
                 NRF_GPIO_PIN_H0D1, NRF_GPIO_PIN_NOSENSE);
    nrf_gpio_cfg(I2C_SDA_PIN, NRF_GPIO_PIN_DIR_INPUT, NRF_GPIO_PIN_INPUT_CONNECT, NRF_GPIO_PIN_NOPULL,
                 NRF_GPIO_PIN_H0D1, NRF_GPIO_PIN_NOSENSE);
}

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
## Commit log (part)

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2022-03-06 Update chassis design
    * Use rounded corners for the caster mount.
    * Add NiMH battery pack underneath the chassis, in front of the motors.
    Will need to add counterweights later to shift center of mass back
    closer to the caster.
    * Added slots for zip ties to fasten the battery pack to the chassis.
    * Added ridges to the bottom of the chassis to stop the battery pack
2022-04-04 First revision of the shield PCB
    I have a few more tweaks that I would like to make before I send this
    off to be manufactured. I ended up going with a 4 layer board as it has
    signal wires going all over the place since I was a bit contrained with
    part placement by most of the Arduino signal pins being on the right
    side of the board and wanting to place connectors on the side closest
    to the part to which they connect.
2022-04-06 Cleaned up silkscreen
    While verifying footprints on PCB printout, I noticed that some
    silkscreen text needed to be moved.
2022-04-11 Add image of my RugRover bot build in progress
2022-04-19 Update CAD design for Chassis
    * Increased thickness from 2.5mm to 5.0mm to increase rigidity of the
    base.
    * Decreased height of standoffs mounting the nRF52 development kit to
    the chassis as the shorter standoffs work better.
    * Updated chassis photos after applying above design changes.
2022-04-21 Test of running MRI on nRF52-DK
    I have checked in an experimental version of my MRI debug monitor that
    allows debugging of the nRF52832 microcontroller over the virutal COM
    port. I have also included a simple blinky test app that builds with
    the Nordic SDK. This simple app can then be debugged from GDB over the
    virtual COM port offered by the nRF52-DK.
    Future Updates:
2022-04-25 PoC - BLE stack running while MRI is debugging
    This commit just shows that MRI can be debugging the main() loop while
    the BLE stack runs in the background via higher priority interrupts.
    The next challenge is to get MRI using that BLE stack as its means of
    communications back to the PC which runs GDB.
2022-04-30 Add MRI as submodule
2022-05-01 Fault handling fixes in mriblue
    * mriFaultHandler() now checks to see if the fault was actually caused
    by MRI when GDB requests accesses to invalid memory locations. This
    code was copied from the existing ThreadDebug library. Before this
    fix, such invalid accesses would cause mriFaultHandler() to enter its
    infinite loop.
    * getInterruptPriority() now shifts off the unused least significant
2022-05-04 Start of load/flash support
    Can now issue the "load" command in GDB and have the code loaded into
    FLASH over the BLE connection.
    I was able to "load" a program into FLASH and then successfully run
    "compare-sections" to verify that the write was successful.
2022-05-06 High priority crashes stored in FLASH for later debugging
    68kB of FLASH are reserved for the storage of this dump:
    * 64kB to store the contents of SRAM at the time of crash.
    * 4kB to store a copy of mriCortexMState, including the
    state of the CPU registers.
    Once the crash has been stored in FLASH, the microcontroller is
    reset. I will later write code to detect the dump in FLASH after the
2022-05-08 mriblue progress report slides
2022-05-12 Add notes to README about mriblue
2022-05-13 Change license of mriblue_boot from GPL to Apache
2022-05-13 Export slides as PDF
2022-05-14 Add "monitor resetbreak" command support
    This command allows the developer to enable or disable breaking into
    the debuggee's Reset_Handler on bootup. This is enabled by default and
    allows the developer to set breakpoints before the code even gets to
    the program's main(). You would disable it though if you want your
    code to just start and run and only halt if it crashes or you manually
    attach the debugger.
2022-05-18 Add OLED_SH1106 driver
    I am now able to display things on my Pololu 1.3" 128x64 1-bit
    monochrome OLED screen https://www.pololu.com/product/3760
    The OLED refresh is written to take maximum advantage of the DMA
    capabilities of the nRF52's SPI master peripheral. The Adafruit GFX
    library just updates an in-memory frame buffer and then the refresh()
    method can be called to start the copy from the in-memory frame buffer
2022-05-22 Auto "monitor reset" after "load"
    No longer need to issue "monitor reset" after every "load" command. It
    no happens automatically in mriblue_boot.
2022-06-05 OLED_SH1106::clearScreen() resets cursor to upper left
2022-06-05 Add quadrature decoding driver notes to README
2022-06-06 Add note about P0.9 & P0.10 and NFC
    These two pins are used for the encoders but require special code to
    make them available as GPIO and the nRF52-DK also needs to be modified
    to remove the 0 ohm R25/R26 resistors and place them on on R27/R28
    instead to move the connection from the NFC antenna to the headers on
    the development kit which connect to my shield.
2022-06-20 QuadratureDecoderSoftware::pinChanged() doesn't need to use atomic op
    The m_count member is only modified by the code in this method which is
    only run from the same ISR. This means it doesn't need to use an atomic
    add operation to modify its value.
2022-06-27 Upgrade to latest MRI version
    MRI now automatically unescapes binary data so it no longer needs to be
    done in the writeToFlash() as it has already been done by MRI by the
    time it gets the data to be written to FLASH.
2022-06-30 Pending DebugMon from fault handlers now handled by MRI
    I pushed the switching from fault mode to DebugMon mode down into the
    core MRI code. This means that even the lower level kernel debugging
    version of MRI will switch into DebugMon mode when debugging faults.
    This eliminates the chance of double faults when GDB attempts to access
    invalid memory regions.
2022-07-07 Refactor semihost usage of errno
    Now have to call mriNewlib_SemihostGetErrNo() to retrieve the errno
    associated with a failed semihost request. I have updated the
    newlib_retarget.c stubs to call this function when an error has been
    detected to then update the Standard C Library's errno value.
    I had to update the nrf52.ld for other changes in this version of the
    MRI library which increased the demand on RAM by one more 32-bit word.
2022-07-09 Moved duplicated files to mriblue_boot/shared
    software/ and mriblue_test/ contained duplicates of files like
    nrf52.ld, gcc_startup_nrf52.S, and newlib_retarget.c. These duplicated
    files have now been moved to mriblue_boot/shared.
2022-07-15 Use RPM for PID velocity
    Switched from encoder ticks per second to RPM for the PID velocity.
2022-07-18 Add SYSLIBS for libs like -lc -lnosys -lm
    The "-u _printf_float" flag was causing me issues since it pulled in
    syscalls from libnosys.a instead of my newlib_retarget.c This happened
    because Makefile.common included the -l -lnosys -lm libs on the linker
    command line before the object files. I now use a SYSLIBS variable to
    include these libraries after the object files if I want instead of
    placing them in the LD_FLAGS variable.
2022-07-18 Update PID limits with latest motor driver limits
    The TB9051FTG Motor Driver doesn't allow immediate switching from one
    direction to another. This update asks the motor driver for its current
    limits and passes them along to the PID loop so that it knows if the
    motor power will be clamped and take it into account in its integral
    windup correction code.
2022-07-18 Update README and photos
    Include notes about a few more drivers: GlobalTimer, PID, and
    DifferentialDrive.
    I also updated the main photo of the RugRover, showing its current
    build progress.
2022-07-21 Make sure that SAADC reading has atleast 1 sample
    When sampling the SAADC channel in
    DualTB9051FTGDrivers::MotorDriver::getCurrentReading(), make sure that
    the reading returned has at least one sample. Based on the timing
    currently used this should be guaranteed but added an assert to make
    sure incase I change the SAADIC and/or PID update rates in the future.
2022-07-23 STDOUT optimization mostly pushed down into MRI
    MRI now uses the 'O' packet instead of the slower "Fwrite" packet when
    writing to file handle 1, STDOUT. This means that mriblue_boot no
    longer needs to wrap mriSemihost_HandleNewlibSemihostRequest() to do
    the same thing. I do still need to wrap the new
    mriSemihost_WriteToFileOrConsole() function to maintain the
    non-blocking nature of these STDOUT writes.
2022-08-07 Update README
    Added some notes about the Navigate class that I recently added to the
    project.
2022-08-10 Add 360 degree turn test
    This can be used later for calibrating the wheel base parameter.
2022-08-11 Update odometry parameters
    This commit updates the wheel diameters from calibration run results.
    Also adds code to run clockwise and counterclockwise around a 0.5m wide
    square.
2022-08-13 Forgot photos for prev commit
    I also fixed some spelling mistakes in software/main.cpp that I noticed
    once I started using the spell checker extension in my code editor.
2022-08-19 Move bonding to switch 1
    Switch 2 is now connected to my IMU so moved it.
2022-09-08 Make TWIM/I2C operations async
    Previously the I2C reads were performed in a blocking fashion which
    meant that it tied up the GPIOTE high priority interrupt waiting for
    them to complete. This commit refactors the code to allow the GPIOTE
    interrupt handler for the falling edge of the accelerometer/magnetometer
    interrupt pin to queue up the reads for the next sample of the
    accelerometer, magnetometer, and gyro:
2022-09-09 Update README
    Added notes about the recently added modules:
    * CircularBuffer
    * I2CAsync
    * AdafruitPrecision9DoF
    * OrientationKalmanFilter
2022-09-11 Slides about my recent mriblue issues
2022-09-14 Add compass heading to navigation test
    Just logs the IMU calculated orientation/heading to the OLED and PC over
    the BLE data connection.
    It waits 5 seconds at the beginning of the test run for the Kalman
    filter to stabilize.
2022-09-14 Spreadsheet used while improving Navigate module
2022-09-15 Fix TWIM ERROR & STOPPED race condition
    Sometimes the I2C master ends up sending 2 stops because the driver gets
    confused when the last byte is NAKed by the slave. Sometimes this
    generates an ERROR event before the STOPPED event and other times it
    happens in the reverse order. I already added a fix for this in the
    blocking code path of the TWIM driver in the Nordic SDK. This commit
    adds a fix for the non-blocking interrupt driven version too.
2022-09-19 Navigate w/ IMU and start of new Kalman filter
    I updated the Navigate module so that it can now use the compass heading
    determined from the IMU based Kalman filter or just use the wheel
    odometry. The test results weren't that good. It seems to be mostly
    related to magnetic interference in the house. Worked better outside.
    Based on the poor 3D orientation Kalman filter, I have started thinking
    about a new Kalman filter which just combines the yaw rate gyro output

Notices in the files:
software/main.cpp:
Copyright (C) 2022  Adam Green (https://github.com/adamgreen)
modify it under the terms of the GNU General Public License
hardware/Motors.kicad_sch:
CC BY-SA 4.0
